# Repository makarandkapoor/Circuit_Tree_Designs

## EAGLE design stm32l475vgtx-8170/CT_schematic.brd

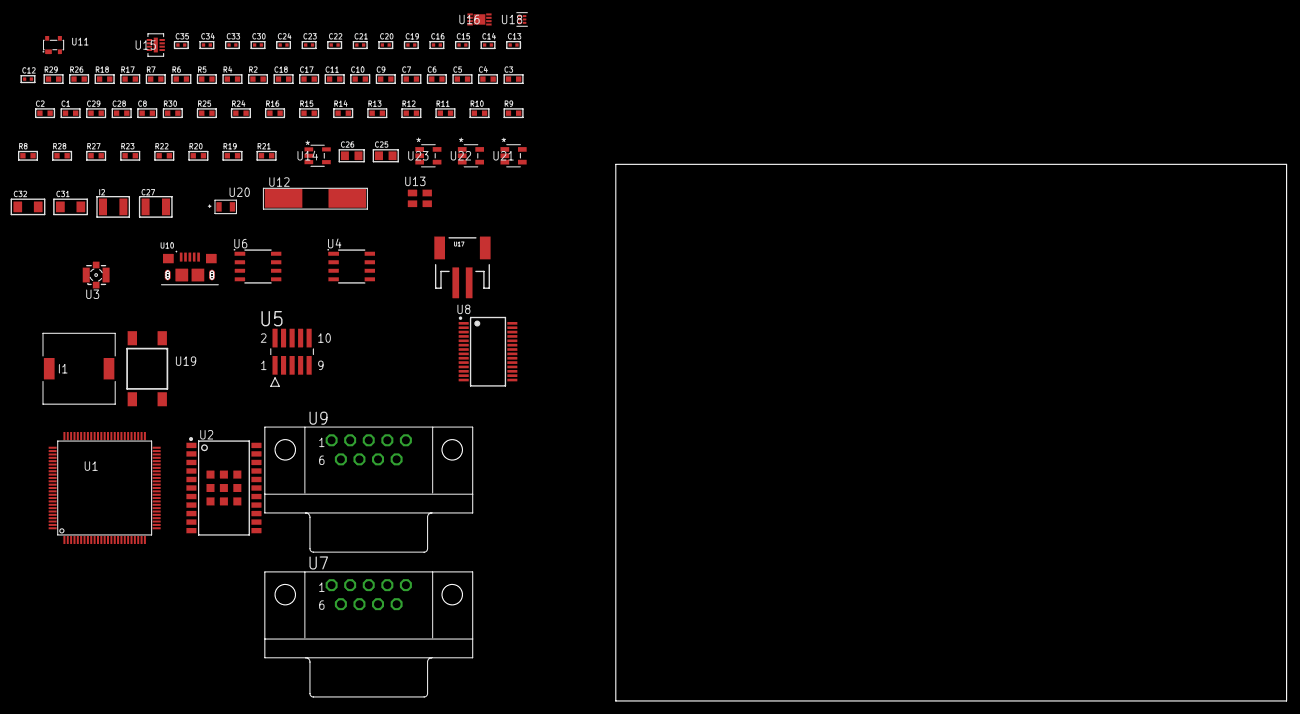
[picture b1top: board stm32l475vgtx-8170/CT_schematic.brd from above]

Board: 2 copper layers, 88 parts (0 on the bottom side), 65 nets, no tracks yet.

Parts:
C1, C11, C17, C18: 1e-06; C0603
C2, C3, C4, C5, C6, C7, C9: 1e-07; C0603
C8: 4.7e-06; C0603
C10: 1e-08; C0603
C12, C13: 1e-11; C0402
C14, C16, C19, C20, C21, C22, C23, C30: 1e-07; C0402
C15, C24, C33, C34, C35: 1e-08; C0402
C25, C26: 1e-05; C0805
C27: 1e-05; C1210
C28: 2.2e-06; C0603
C29: 2.2e-07; C0603
C31, C32: 1e-05; C1206
I1: 2.5e-06; DR1040
I2: 1e-05; L1210
R2: 1000.0; R0603
R4, R5: 4700.0; R0603
R6, R7: 2200.0; R0603
R8, R9, R10, R11, R12, R13, R14, R15, R16, R24, R25, R30: 10000.0; R0603
R17: 5.0; R0603
R18: 120.0; R0603
R19, R22: 100000.0; R0603
R20: 220000.0; R0603
R21: 1000000.0; R0603
R23: 560000.0; R0603
R26: 9100.0; R0603
R27: 680000.0; R0603
R28: 120000.0; R0603
R29: 2000.0; R0603
U1: STM32L475VGT6; LQFP100
U2: A2200-A
U3: 73412-0114; COAXIAL_C
U4: AT25M02-SSHD-T; SOIC-8
U5: FTSH-105-01-L-DV-K; SAMTEC_FTSH-105-01-L-DV-K
U6: MCP2562-E/SN; SOIC-8
U7, U9: 182-009-113R531; 182-009-MALE
U8: ST3241EBPR; SSOP-28
U10: 10118193-0001LF; FCI_10118193-0001LF
U11: prtr5v0u2ax; SOT143B
U12: ABLS-25.000MHZ-B2F-T
U13: ASEK-32.768KHz-ECST; ASEK
U14: ltc3406es5; TSOT-23-5
U15: LT3494AEDDB#TRMPBF; DFN-8_DDB
U16: MCP73831T-2ACI/MC; DFN8_2X3MC
U17: S2B-PH-SM4-TB(LF)(SN); JST-2-SMD
U18: TPS3895ADRYR; SON-6
U19: 4-1437565-2; SW_4-1437565-2
U20: Q65110A2395; LGM67K-G1J2-24-Z
U21, U22, U23: nc7sz125m5x; NC7SZ125M5X

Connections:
CLK_CRYSTAL_U1_12: C12.1, U1.12, U12.1
CLK_CRYSTAL_U1_13: C13.1, U1.13, U12.2
CLK_U1_8: U1.8, U13.3
GND: C1.2, C2.2, C3.2, C4.2, C5.2, C6.2, C7.2, C8.2, C9.2, C10.2, C11.2, C12.2, C13.2, C14.2, C15.2, C16.2, C17.2, C18.2, C19.2, C22.2, C23.2, C24.2, C25.2, C26.1, C26.2, C27.2, C28.2, C29.2, C30.2, C31.2, C32.2, C33.2, C34.2, C35.2, R2.2, R8.2, R16.2, R17.2, R20.2, R26.2, R28.2, R29.2, U1.10, U1.19, U1.20, U1.27, U1.49, U1.74, U1.99, U2.7, U2.8, U2.23, U2.24, U2.25, U2.26, U2.27, U2.28, U2.29, U2.30, U2.31, U4.4, U5.3, U5.5, U6.2, U6.8, U7.5, U8.23, U8.25, U9.5, U10.5, U10.6, U10.7, U10.8, U10.9, U11.1, U13.2, U14.2, U15.2, U15.9, U16.6, U16.9, U17.2, U18.2, U20.C, U21.2, U21.3, U22.1, U22.3, U23.1, U23.3
INPUT_USBPOWER_5V: C31.1, R30.2, U1.68, U10.1, U11.4, U16.1, U16.2
NET_U1_14: R5.1, U1.14, U23.4
NET_U1_92: R6.1, U1.92, U2.15
NET_U1_93: R7.1, U1.93, U2.16
NET_U1_94: R8.1, U1.94
NET_U1_98: U19.3, U19.4
NET_U2_2: R9.2, U2.2
NET_U2_17: R9.1, U2.17
NET_U2_22: R4.1, U2.22, U22.4
NET_U3_1: U2.11, U3.1
NET_U3_2: U2.10, U3.2, U3.3, U3.4
NET_U4_3: R10.1, U4.3
NET_U4_7: R12.1, U4.7
NET_U5_9: R17.1, U5.9
NET_U6_6: R18.2, U6.6
NET_U7_2: R18.2, U6.6, U7.2
NET_U7_3: R18.1, U6.7, U7.3
NET_U8_1: C21.1, U8.1
NET_U8_2: C21.2, U8.2
NET_U8_3: C23.1, U8.3
NET_U8_22: R19.1, U8.22
NET_U8_24: C20.2, U8.24
NET_U8_27: C22.1, U8.27
NET_U8_28: C20.1, U8.28
NET_U9_2: U8.4, U9.2
NET_U9_3: U8.9, U9.3
NET_U9_7: U8.5, U9.7
NET_U9_8: U8.10, U9.8
NET_U14_3: I1.1, U14.3
NET_U14_5: R20.1, R21.1, U14.5
NET_U14_ATNET_3: I1.2, R21.2
NET_U15_1: I2.1, U15.1
NET_U15_5: R22.1, U15.5
NET_U15_6: R23.1, U15.6
NET_U15_8: C29.1, U15.8
NET_U16_5: R30.1, U16.5
NET_U16_8: R29.1, U16.8
NET_U18_1: R25.1, R26.1, U18.1
NET_U18_3: R27.2, R28.1, U18.3
NET_U18_4: R24.1, U18.4, U21.4, U22.2, U23.2
NET_U19_1: R2.1, U19.1, U19.2
PROC_CAN1_RX: U1.81, U6.4
PROC_CAN1_TX: U1.82, U6.1
PROC_LPUART1_CTS: U1.52, U8.13
PROC_LPUART1_RTS: U1.51, U8.18
PROC_LPUART1_RX: U1.15, U8.19
PROC_LPUART1_TX: U1.16, U8.14
PROC_SPI1_MISO: U1.31, U4.2
PROC_SPI1_MOSI: U1.32, U4.5
PROC_SPI1_NSS: R11.1, U1.29, U4.1
PROC_SPI1_SCK: U1.30, U4.6
PROC_SYS_JTCK_SWCLK: R16.1, U1.76, U5.4
PROC_SYS_JTDI: R14.1, U1.77, U5.8
PROC_SYS_JTDO_SWO: U1.89, U5.6
PROC_SYS_JTMS_SWDIO: R15.1, U1.72, U5.2
PROC_USB_OTG_FS_DM: U1.70, U10.2, U11.3
PROC_USB_OTG_FS_DP: U1.71, U10.3, U11.2
RST_OUT_U5_JTAG_RST_B: R13.1, U5.10, U21.1
VCC_S1_3V7: C25.1, C27.1, C32.1, I2.2, R22.2, U14.4, U15.3, U15.4, U16.3, U16.4, U17.1
VCC_TIER1_3V3: C1.1, C2.1, C3.1, C4.1, C5.1, C6.1, C7.1, C8.1, C9.1, C10.1, C11.1, C14.1, C15.1, C16.1, C18.1, C19.1, C24.1, C26.2, C30.1, C33.1, C34.1, C35.1, I1.2, R4.2, R5.2, R6.2, R7.2, R10.2, R11.2, R12.2, R13.2, R14.2, R15.2, R19.2, R21.2, R24.2, R25.2, R27.1, U1.6, U1.11, U1.21, U1.22, U1.28, U1.50, U1.73, U1.75, U1.100, U2.20, U4.8, U5.1, U6.5, U8.26, U13.4, U18.6, U21.5, U22.5, U23.5
VCC_TIER1_5V0: C17.1, C28.1, R23.2, U6.3, U15.7

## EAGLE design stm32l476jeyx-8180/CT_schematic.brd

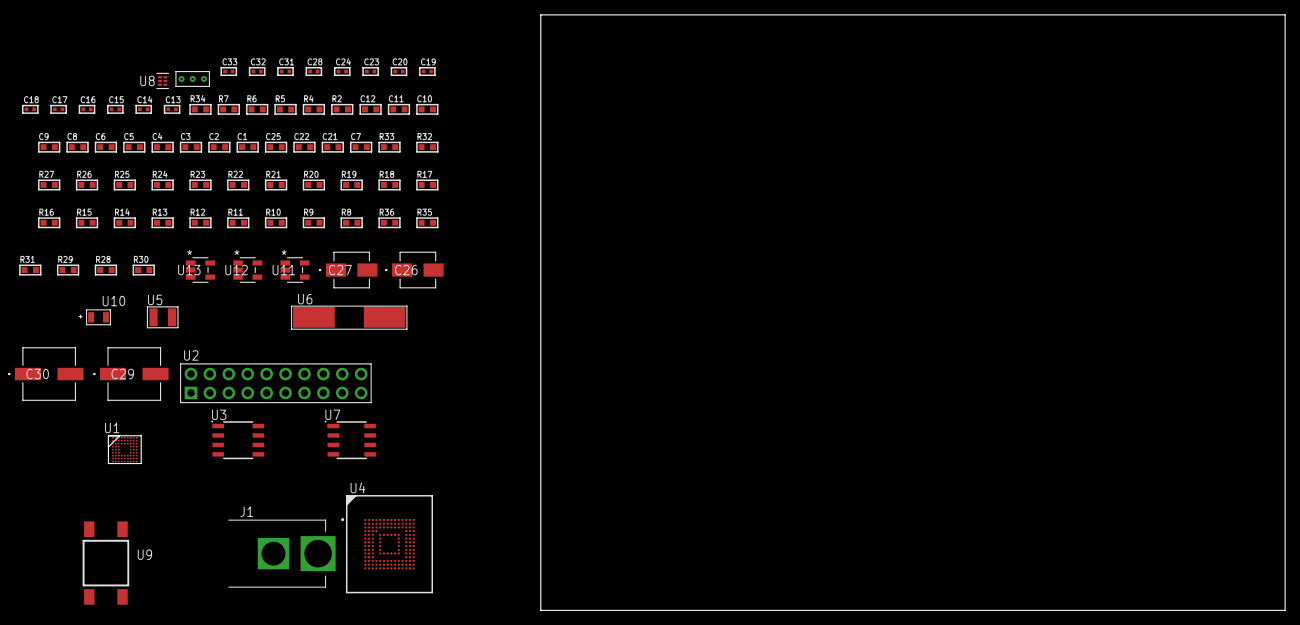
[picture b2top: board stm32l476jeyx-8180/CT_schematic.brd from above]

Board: 2 copper layers, 158.1 x 80.0 mm, 82 parts (0 on the bottom side), 43 nets, no tracks yet.

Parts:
C1, C12: 1e-06; C0603
C2, C3, C4, C5, C6, C8, C9, C10: 1e-07; C0603
C7: 4.7e-06; C0603
C11: 1e-08; C0603
C13, C14, C15, C16: 1e-11; C0402
C17, C18, C20, C23, C24, C28: 1e-07; C0402
C19, C31, C32, C33: 1e-08; C0402
C21, C22, C25: 2.2e-06; C0603
C26: 1e-06; EXV-9B
C27: 2.2e-06; EXV-9B
C29, C30: 0.0001; EXV-9H
J1: PJ-037B; PJ-037B_PACKAGE
R2: 1000.0; R0603
R4, R5: 4700.0; R0603
R6, R7: 2200.0; R0603
R8, R9, R10, R11, R12, R13, R14, R15, R16, R17, R32, R33: 10000.0; R0603
R18, R19, R20, R21, R22, R23, R24, R25, R26, R27: 34000.0; R0603
R28, R29, R31: 100000.0; R0603
R30: 164658.62; R0603
R34: 9100.0; R0603
R35: 680000.0; R0603
R36: 120000.0; R0603
U1: STM32L476JEY6; WLCSP72
U2: TST-110-05-T-D-RA
U3: 24AA1025T-I/SN; SOIC-8
U4: mtfc4gmcdm; TFBGA-153
U5: ABS07-32.768KHZ-7-T
U6: ABLS-25.000MHZ-B2F-T
U7: LP2954AIMX/NOPB; LP2954
U8: TPS3895ADRYR; SON-6
U9: 4-1437565-2; SW_4-1437565-2
U10: Q65110A2395; LGM67K-G1J2-24-Z
U11, U12, U13: nc7sz125m5x; NC7SZ125M5X
U14: Dummy; DUMMY_PACKAGE_186

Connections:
CLK_CRYSTAL_U1_C8: C13.1, U1.C8, U5.1
CLK_CRYSTAL_U1_C9: C14.1, U1.C9, U5.2
CLK_CRYSTAL_U1_D8: C15.1, U1.D8, U6.1
CLK_CRYSTAL_U1_D9: C16.1, U1.D9, U6.2
GND: C1.2, C2.2, C3.2, C4.2, C5.2, C6.2, C7.2, C8.2, C9.2, C10.2, C11.2, C12.2, C13.2, C14.2, C15.2, C16.2, C17.2, C18.2, C19.2, C20.2, C21.2, C22.2, C23.2, C24.2, C25.2, C26.2, C27.2, C28.2, C29.2, C30.2, C31.2, C32.2, C33.2, J1.2, R2.2, R8.2, R14.2, R17.2, R31.2, R34.2, R36.2, U1.A8, U1.B1, U1.G9, U1.J2, U1.J9, U2.4, U2.6, U2.8, U2.10, U2.12, U2.14, U2.16, U2.18, U2.20, U3.4, U3.7, U4.C4, U4.E7, U4.G5, U4.H10, U4.K8, U4.N2, U4.N5, U4.P4, U4.P6, U7.4, U8.2, U10.C, U11.2, U11.3, U12.1, U12.3, U13.1, U13.3, U14.1
NET_U1_A5: R6.1, U1.A5, U3.6
NET_U1_A7: R7.1, U1.A7, U3.5
NET_U1_D7: R8.1, U1.D7
NET_U1_E9: R5.1, U1.E9, U13.4
NET_U1_J7: U9.3, U9.4
NET_U2_19: R14.1, U2.19
NET_U3_1: R16.1, U3.1
NET_U3_2: R17.1, U3.2
NET_U3_3: R15.1, U3.3
NET_U4_C2: C22.1, C23.1, U4.C2
NET_U4_K5: R4.1, U4.K5, U12.4
NET_U7_3: R29.1, U7.3
NET_U7_5: R28.1, U7.5
NET_U7_7: R30.2, R31.1, U7.7
NET_U8_1: R33.1, R34.1, U8.1
NET_U8_3: R35.2, R36.1, U8.3
NET_U8_4: R32.1, U8.4, U11.4, U12.2, U13.2
NET_U9_1: R2.1, U9.1, U9.2
PROC_PG9: U1.A4, U14.2
PROC_PG10: U1.B4, U14.3
PROC_SDMMC1_CK: R27.1, U1.B3, U4.M6
PROC_SDMMC1_CMD: R26.1, U1.A3, U4.M5
PROC_SDMMC1_D0: R18.1, U1.F2, U4.A3
PROC_SDMMC1_D1: R19.1, U1.E1, U4.A4
PROC_SDMMC1_D2: R20.1, U1.D3, U4.A5
PROC_SDMMC1_D3: R21.1, U1.C3, U4.B2
PROC_SDMMC1_D4: R22.1, U1.E7, U4.B3
PROC_SDMMC1_D5: R23.1, U1.E8, U4.B4
PROC_SDMMC1_D6: R24.1, U1.F3, U4.B5
PROC_SDMMC1_D7: R25.1, U1.F1, U4.B6
PROC_SYS_JTCK_SWCLK: R12.1, U1.B2, U2.9
PROC_SYS_JTDI: R10.1, U1.A2, U2.5
PROC_SYS_JTDO_SWO: U1.A6, U2.13
PROC_SYS_JTMS_SWDIO: R11.1, U1.C2, U2.7
PROC_SYS_JTRST: R9.1, U1.C6, U2.3
RST_OUT_U2_SRESET_B: R13.1, U2.15, U11.1
VCC_S1_5V2: C26.1, C29.1, C30.1, J1.1, R29.2, U7.8
VCC_TIER1_3V3: C1.1, C2.1, C3.1, C4.1, C5.1, C6.1, C7.1, C8.1, C9.1, C10.1, C11.1, C12.1, C17.1, C18.1, C19.1, C20.1, C21.1, C24.1, C25.1, C27.1, C28.1, C31.1, C32.1, C33.1, R4.2, R5.2, R6.2, R7.2, R9.2, R10.2, R11.2, R12.2, R13.2, R15.2, R16.2, R18.2, R19.2, R20.2, R21.2, R22.2, R23.2, R24.2, R25.2, R26.2, R27.2, R28.2, R30.1, R32.2, R33.2, R35.1, U1.A1, U1.A9, U1.B6, U1.B9, U1.G8, U1.H9, U1.J1, U1.J8, U2.1, U2.2, U3.8, U4.C6, U4.E6, U4.F5, U4.J10, U4.K9, U4.M4, U4.N4, U4.P3, U4.P5, U7.1, U8.6, U11.5, U12.5, U13.5

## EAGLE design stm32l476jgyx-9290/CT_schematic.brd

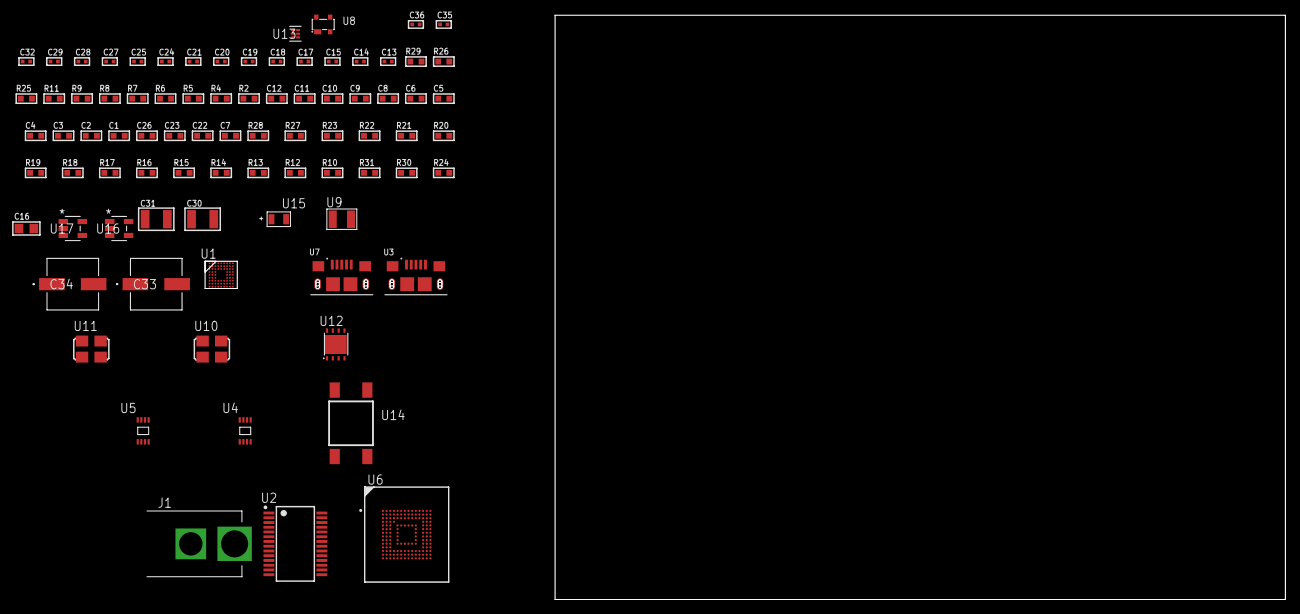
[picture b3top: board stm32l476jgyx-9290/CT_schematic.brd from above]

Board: 2 copper layers, 83 parts (0 on the bottom side), 46 nets, no tracks yet.

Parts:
C1, C12: 1e-06; C0603
C2, C3, C4, C5, C6, C8, C9, C10: 1e-07; C0603
C7: 4.7e-06; C0603
C11: 1e-08; C0603
C13, C14: 1e-11; C0402
C15, C17, C18, C21, C24, C25, C32: 1e-07; C0402
C16: 4.7e-06; C0805
C19, C20, C27, C28, C29, C35, C36: 1e-08; C0402
C22, C23, C26: 2.2e-06; C0603
C30, C31: 1e-05; C1210
C33, C34: 0.0001; EXV-9H
J1: PJ-037B; PJ-037B_PACKAGE
R2, R26: 1000.0; R0603
R4, R5, R11: 4700.0; R0603
R6, R7, R8, R9: 2200.0; R0603
R10, R12, R13, R27, R28: 10000.0; R0603
R14, R15, R16, R17, R18, R19, R20, R21, R22, R23: 34000.0; R0603
R24: 100000.0; R0603
R25: 2231.0; R0603
R29: 9100.0; R0603
R30: 680000.0; R0603
R31: 120000.0; R0603
U1: STM32L476JGY7; WLCSP72
U2: FT232RL-REEL; SSOP-28
U3, U7: 10118193-0001LF; FCI_10118193-0001LF
U4: 24AA01T-I/MNY; TDFN-8/6MM
U5: 24AA02T-I/MNY; TDFN-8/6MM
U6: mtfc4gmcdm; TFBGA-153
U8: prtr5v0u2ax; SOT143B
U9: ABS07-32.768KHZ-7-T
U10: ASFL1-12MHZ-NCS; ASFL1
U11: ASFL1-25MHZ-NCS; ASFL1
U12: LP3878SDX-ADJ/NOPB; WSON-8
U13: TPS3895ADRYR; SON-6
U14: 4-1437565-2; SW_4-1437565-2
U15: Q65110A2395; LGM67K-G1J2-24-Z
U16, U17: nc7sz125m5x; NC7SZ125M5X

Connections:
CLK_CRYSTAL_U1_C8: C13.1, U1.C8, U9.1
CLK_CRYSTAL_U1_C9: C14.1, U1.C9, U9.2
CLK_U1_D9: U1.D9, U11.3
CLK_U2_27: U2.27, U10.3
GND: C1.2, C2.2, C3.2, C4.2, C5.2, C6.2, C7.2, C8.2, C9.2, C10.2, C11.2, C12.2, C13.2, C14.2, C15.2, C16.2, C17.2, C18.2, C19.2, C20.2, C21.2, C22.2, C23.2, C24.2, C25.2, C26.2, C27.2, C28.2, C29.2, C30.2, C31.2, C32.2, C33.2, C34.2, C35.2, C36.2, J1.2, R2.2, R10.2, R13.2, R26.2, R29.2, R31.2, U1.A8, U1.B1, U1.G9, U1.J2, U1.J9, U2.7, U2.18, U2.21, U2.25, U2.26, U3.5, U3.6, U3.7, U3.8, U3.9, U4.4, U4.7, U5.4, U5.7, U6.C4, U6.E7, U6.G5, U6.H10, U6.K8, U6.N2, U6.N5, U6.P4, U6.P6, U7.5, U7.6, U7.7, U7.8, U7.9, U8.1, U10.2, U11.2, U12.3, U12.PAD, U13.2, U15.C, U16.1, U16.3, U17.1, U17.3
NET_U1_A5: R6.1, U1.A5, U4.6
NET_U1_A7: R7.1, U1.A7, U4.5
NET_U1_D7: R10.1, U1.D7
NET_U1_E9: R5.1, U1.E9, U17.4
NET_U1_G2: R9.1, U1.G2, U5.5
NET_U1_H3: R8.1, U1.H3, U5.6
NET_U1_J7: U14.3, U14.4
NET_U2_14: R12.1, U2.14
NET_U2_17: C17.1, U2.17
NET_U2_19: R13.1, U2.19
NET_U3_1: R11.1, U3.1
NET_U3_2: U2.16, U3.2
NET_U3_3: U2.15, U3.3
NET_U6_C2: C23.1, C24.1, U6.C2
NET_U6_K5: R4.1, U6.K5, U16.4
NET_U12_1: C29.1, U12.1
NET_U12_6: R25.2, R26.1, U12.6
NET_U12_8: R24.1, U12.8
NET_U13_1: R28.1, R29.1, U13.1
NET_U13_3: R30.2, R31.1, U13.3
NET_U13_4: R27.1, U13.4, U16.2, U17.2
NET_U14_1: R2.1, U14.1, U14.2
PROC_LPUART1_CTS: U1.H2, U2.3
PROC_LPUART1_RTS: U1.H1, U2.11
PROC_LPUART1_RX: U1.F9, U2.1
PROC_LPUART1_TX: U1.F8, U2.5
PROC_SDMMC1_CK: R23.1, U1.B3, U6.M6
PROC_SDMMC1_CMD: R22.1, U1.A3, U6.M5
PROC_SDMMC1_D0: R14.1, U1.F2, U6.A3
PROC_SDMMC1_D1: R15.1, U1.E1, U6.A4
PROC_SDMMC1_D2: R16.1, U1.D3, U6.A5
PROC_SDMMC1_D3: R17.1, U1.C3, U6.B2
PROC_SDMMC1_D4: R18.1, U1.E7, U6.B3
PROC_SDMMC1_D5: R19.1, U1.E8, U6.B4
PROC_SDMMC1_D6: R20.1, U1.F3, U6.B5
PROC_SDMMC1_D7: R21.1, U1.F1, U6.B6
PROC_USB_OTG_FS_DM: U1.D1, U7.2, U8.3
PROC_USB_OTG_FS_DP: U1.C1, U7.3, U8.2
PROC_USB_OTG_FS_VBUS: U1.E3, U7.1, U8.4
VCC_S1_14V6: C30.1, C33.1, C34.1, J1.1, R24.2, U12.4
VCC_TIER1_3V3: C1.1, C2.1, C3.1, C4.1, C5.1, C6.1, C7.1, C8.1, C9.1, C10.1, C11.1, C12.1, C15.1, C16.1, C18.1, C19.1, C20.1, C21.1, C22.1, C25.1, C26.1, C27.1, C28.1, C31.1, C32.1, C35.1, C36.1, R4.2, R5.2, R6.2, R7.2, R8.2, R9.2, R12.2, R14.2, R15.2, R16.2, R17.2, R18.2, R19.2, R20.2, R21.2, R22.2, R23.2, R25.1, R27.2, R28.2, R30.1, U1.A1, U1.A9, U1.B6, U1.B9, U1.G8, U1.H9, U1.J1, U1.J8, U2.4, U2.20, U4.8, U5.8, U6.C6, U6.E6, U6.F5, U6.J10, U6.K9, U6.M4, U6.N4, U6.P3, U6.P5, U10.4, U11.4, U12.5, U13.6, U16.5, U17.5

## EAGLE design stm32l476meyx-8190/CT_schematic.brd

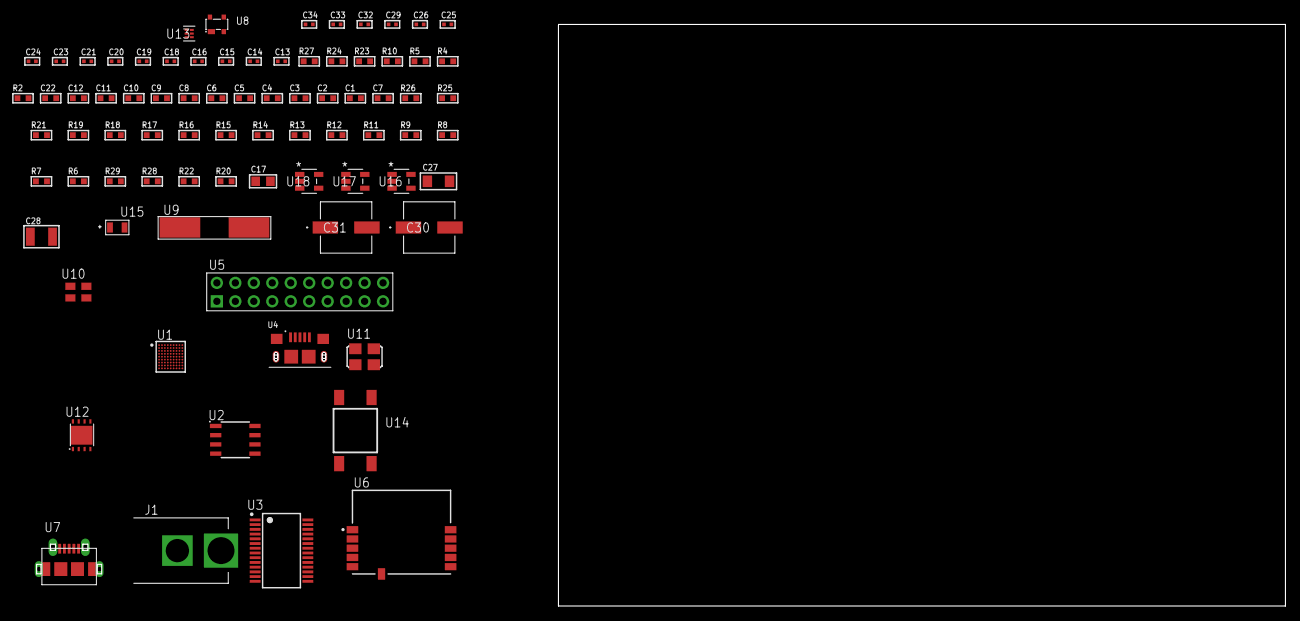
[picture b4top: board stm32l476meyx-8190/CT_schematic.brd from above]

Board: 2 copper layers, 171.8 x 80.0 mm, 80 parts (0 on the bottom side), 50 nets, no tracks yet.

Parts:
C1, C12, C22: 1e-06; C0603
C2, C3, C4, C5, C6, C8, C9, C10: 1e-07; C0603
C7: 4.7e-06; C0603
C11: 1e-08; C0603
C13, C14: 1e-11; C0402
C15, C24, C25, C26, C32, C33, C34: 1e-08; C0402
C16, C18, C19, C20, C21, C23, C29: 1e-07; C0402
C17: 4.7e-06; C0805
C27: 1e-05; C1206
C28: 1e-05; C1210
C30, C31: 0.0001; EXV-9H
J1: PJ-037B; PJ-037B_PACKAGE
R2, R24: 1000.0; R0603
R4, R5, R10: 4700.0; R0603
R6, R7, R8, R9, R11, R12, R13, R14, R15, R16, R17, R18, R19, R25, R26: 10000.0; R0603
R20, R22: 100000.0; R0603
R21: 47000.0; R0603
R23: 2231.0; R0603
R27: 9100.0; R0603
R28: 680000.0; R0603
R29: 120000.0; R0603
U1: STM32L476MEY6; WLCSP81
U2: AT25128B-SSHL-T; SOIC-8
U3: FT232RL-REEL; SSOP-28
U4: 10118193-0001LF; FCI_10118193-0001LF
U5: TST-110-05-T-D-RA
U6: SPBTLE-RF; XCVR_SPBTLE-RF
U7: 47590-0001; MICRO_USB_AB
U8: prtr5v0u2ax; SOT143B
U9: ABLS-25.000MHZ-B2F-T
U10: ASEK-32.768KHz-ECST; ASEK
U11: ASFL1-12MHZ-NCS; ASFL1
U12: LP3878SDX-ADJ/NOPB; WSON-8
U13: TPS3895ADRYR; SON-6
U14: 4-1437565-2; SW_4-1437565-2
U15: Q65110A2395; LGM67K-G1J2-24-Z
U16, U17, U18: nc7sz125m5x; NC7SZ125M5X

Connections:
CLK_CRYSTAL_U1_D8: C13.1, U1.D8, U9.1
CLK_CRYSTAL_U1_D9: C14.1, U1.D9, U9.2
CLK_U1_C9: U1.C9, U10.3
CLK_U3_27: U3.27, U11.3
GND: C1.2, C2.2, C3.2, C4.2, C5.2, C6.2, C7.2, C8.2, C9.2, C10.2, C11.2, C12.2, C13.2, C14.2, C15.2, C16.2, C17.2, C18.2, C19.2, C20.2, C21.2, C22.2, C23.2, C24.2, C25.2, C26.2, C27.2, C28.2, C29.2, C30.2, C31.2, C32.2, C33.2, C34.2, J1.2, R2.2, R6.2, R12.2, R18.2, R20.2, R21.2, R24.2, R27.2, R29.2, U1.A8, U1.B1, U1.G9, U1.J2, U1.J9, U2.4, U3.7, U3.18, U3.21, U3.25, U3.26, U4.5, U4.6, U4.7, U4.8, U4.9, U5.4, U5.6, U5.8, U5.10, U5.12, U5.14, U5.16, U5.18, U5.20, U6.6, U7.5, U7.6, U7.7, U7.8, U7.9, U8.1, U10.2, U11.2, U12.3, U12.PAD, U13.2, U15.C, U16.2, U16.3, U17.1, U17.3, U18.1, U18.3
NET_U1_D7: R6.1, U1.D7
NET_U1_E9: R5.1, U1.E9, U18.4
NET_U1_J7: U14.3, U14.4
NET_U2_3: R7.1, U2.3
NET_U2_7: R9.1, U2.7
NET_U3_14: R11.1, U3.14
NET_U3_17: C18.1, U3.17
NET_U3_19: R12.1, U3.19
NET_U4_1: R10.1, U4.1
NET_U4_2: U3.16, U4.2
NET_U4_3: U3.15, U4.3
NET_U5_19: R18.1, U5.19
NET_U6_11: R4.1, U6.11, U17.4
NET_U12_1: C26.1, U12.1
NET_U12_6: R23.2, R24.1, U12.6
NET_U12_8: R22.1, U12.8
NET_U13_1: R26.1, R27.1, U13.1
NET_U13_3: R28.2, R29.1, U13.3
NET_U13_4: R25.1, U13.4, U16.4, U17.2, U18.2
NET_U14_1: R2.1, U14.1, U14.2
PROC_GPIO_TO_U6_SPI_IRQ: R21.1, U1.A3, U6.4
PROC_LPUART1_CTS: U1.H2, U3.3
PROC_LPUART1_RTS: U1.H1, U3.11
PROC_LPUART1_RX: U1.F9, U3.1
PROC_LPUART1_TX: U1.F8, U3.5
PROC_SPI1_MISO: U1.H5, U6.8
PROC_SPI1_MOSI: U1.C7, U6.9
PROC_SPI1_NSS: R19.1, U1.G5, U6.10
PROC_SPI1_SCK: R20.1, U1.H6, U6.7
PROC_SPI2_MISO: U1.F7, U2.2
PROC_SPI2_MOSI: U1.E5, U2.5
PROC_SPI2_NSS: R8.1, U1.E8, U2.1
PROC_SPI2_SCK: U1.H3, U2.6
PROC_SYS_JTCK_SWCLK: R16.1, U1.B2, U5.9
PROC_SYS_JTDI: R14.1, U1.A2, U5.5
PROC_SYS_JTDO_SWO: U1.A6, U5.13
PROC_SYS_JTMS_SWDIO: R15.1, U1.C2, U5.7
PROC_SYS_JTRST: R13.1, U1.C6, U5.3
PROC_USB_OTG_FS_DM: U1.D1, U7.2, U8.3
PROC_USB_OTG_FS_DP: U1.C1, U7.3, U8.2
PROC_USB_OTG_FS_ID: U1.D2, U7.4
PROC_USB_OTG_FS_VBUS: U1.E3, U7.1, U8.4
RST_OUT_U5_SRESET_B: R17.1, U5.15, U16.1
VCC_S1_10V0: C27.1, C30.1, C31.1, J1.1, R22.2, U12.4
VCC_TIER1_3V3: C1.1, C2.1, C3.1, C4.1, C5.1, C6.1, C7.1, C8.1, C9.1, C10.1, C11.1, C12.1, C15.1, C16.1, C17.1, C19.1, C20.1, C21.1, C22.1, C23.1, C24.1, C25.1, C28.1, C29.1, C32.1, C33.1, C34.1, R4.2, R5.2, R7.2, R8.2, R9.2, R11.2, R13.2, R14.2, R15.2, R16.2, R17.2, R19.2, R23.1, R25.2, R26.2, R28.1, U1.A1, U1.A9, U1.B6, U1.B9, U1.E4, U1.G8, U1.H9, U1.J1, U1.J8, U2.8, U3.4, U3.20, U5.1, U5.2, U6.5, U10.4, U11.4, U12.5, U13.6, U16.5, U17.5, U18.5

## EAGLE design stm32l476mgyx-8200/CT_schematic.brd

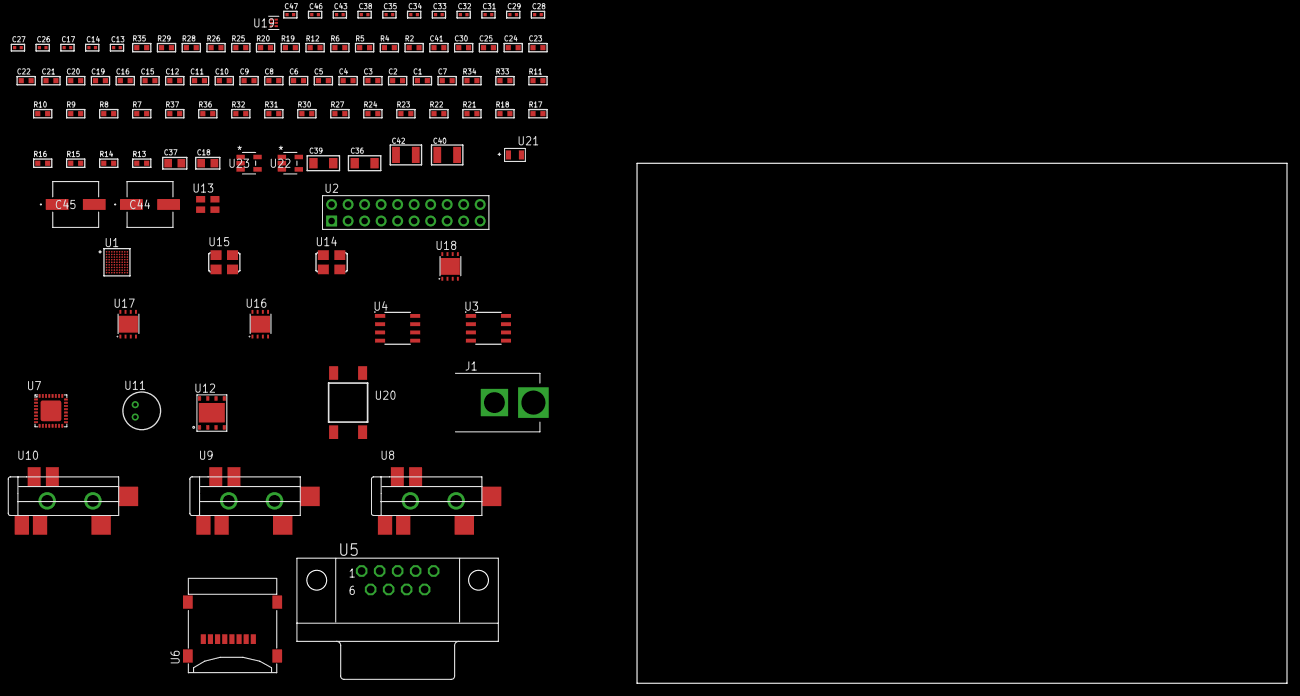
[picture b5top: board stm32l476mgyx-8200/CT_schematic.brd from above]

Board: 2 copper layers, 100.0 x 80.0 mm, 106 parts (0 on the bottom side), 65 nets, no tracks yet.

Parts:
C1, C12, C15, C16, C19, C20, C21, C22, C23, C24, C25, C30, C41: 1e-06; C0603
C2, C3, C4, C5, C6, C8, C9, C10: 1e-07; C0603
C7: 4.7e-06; C0603
C11: 1e-08; C0603
C13, C17, C26, C27, C28, C29, C31, C43: 1e-07; C0402
C14, C32, C33, C34, C35, C38, C46, C47: 1e-08; C0402
C18, C37: 1e-05; C0805
C36, C39: 1e-05; C1206
C40, C42: 1e-05; C1210
C44, C45: 0.0001; EXV-9H
J1: PJ-037B; PJ-037B_PACKAGE
R2, R26, R29: 1000.0; R0603
R4: 4700.0; R0603
R5, R6: 2200.0; R0603
R7, R8, R9, R10, R11, R33, R34: 10000.0; R0603
R12: 120.0; R0603
R13, R14, R15, R16, R17, R18, R21, R22, R23, R24, R27, R30, R32: 100000.0; R0603
R19, R20: 1270.0; R0603
R25: 200.0; R0603
R28: 2231.0; R0603
R31: 300000.0; R0603
R35: 9100.0; R0603
R36: 680000.0; R0603
R37: 120000.0; R0603
U1: STM32L476MGY6; WLCSP81
U2: TST-110-05-T-D-RA
U3: 24AA1025T-I/SN; SOIC-8
U4: MCP2562-E/SN; SOIC-8
U5: 182-009-113R531; 182-009-MALE
U6: 0472192001; MOLEX_47219-2001
U7: SGTL5000XNAA3; QFN-32
U8, U9, U10: SJ-43515TS-SMT-TR
U11: WM-64PCT; WM-64PC
U12: SST26VF032B-104I/MF; WFDN-8
U13: ASEK-32.768KHz-ECST; ASEK
U14: ASFL-24.57MHZ-NCS; ASFL1
U15: ASFL1-25MHZ-NCS; ASFL1
U16, U17: LP3878SDX-ADJ/NOPB; WSON-8
U18: LP2951ACSDX/NOPB; WSON-8
U19: TPS3895ADRYR; SON-6
U20: 4-1437565-2; SW_4-1437565-2
U21: Q65110A2395; LGM67K-G1J2-24-Z
U22, U23: nc7sz125m5x; NC7SZ125M5X

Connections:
CLK_U1_C9: U1.C9, U13.3
CLK_U1_D9: U1.D9, U15.3
CLK_U7_21: U7.21, U14.3
GND: C1.2, C2.2, C3.2, C4.2, C5.2, C6.2, C7.2, C8.2, C9.2, C10.2, C11.2, C12.2, C13.2, C14.2, C15.2, C16.2, C17.2, C18.2, C26.2, C27.2, C28.2, C29.2, C30.2, C31.2, C32.2, C33.2, C34.2, C35.2, C36.2, C37.2, C38.2, C39.2, C40.2, C41.2, C42.2, C43.2, C44.2, C45.2, C46.2, C47.2, J1.2, R2.2, R7.2, R20.2, R26.2, R29.2, R32.2, R35.2, R37.2, U1.A8, U1.B1, U1.G9, U1.J2, U1.J9, U2.4, U2.6, U2.8, U2.10, U2.12, U2.14, U2.16, U2.18, U2.20, U3.4, U3.7, U4.2, U4.8, U5.5, U6.6, U6.G1, U6.G2, U6.G3, U6.G4, U7.1, U7.3, U7.7, U7.EXP, U9.1, U10.1, U11.2, U12.4, U12.9, U13.2, U14.2, U15.2, U16.3, U16.PAD, U17.3, U17.PAD, U18.3, U18.4, U18.PAD, U19.2, U21.C, U22.2, U22.3, U23.1, U23.3
NET_U1_A5: R5.1, U1.A5, U3.6
NET_U1_A7: R6.1, U1.A7, U3.5
NET_U1_D7: R7.1, U1.D7
NET_U1_E9: R4.1, U1.E9, U23.4
NET_U1_J7: U20.3, U20.4
NET_U3_1: R10.1, U3.1
NET_U3_2: R11.1, U3.2
NET_U3_3: R9.1, U3.3
NET_U4_6: R12.2, U4.6
NET_U5_2: R12.2, U4.6, U5.2
NET_U5_3: R12.1, U4.7, U5.3
NET_U7_10: C29.1, U7.10
NET_U7_29: R19.1, U7.29
NET_U7_31: R20.1, U7.31
NET_U8_1: U7.4, U8.1
NET_U8_2: U7.2, U8.2
NET_U8_5: U7.6, U8.5
NET_U9_2: C20.1, U9.2
NET_U9_5: C19.1, U9.5
NET_U10_2: C22.1, C23.1, U10.2
NET_U10_5: C21.1, U10.5
NET_U10_13: C22.2, C23.2
NET_U11_1: C24.1, C25.1, C30.1, U7.16, U11.1
NET_U11_15: C24.2, C25.2
NET_U16_1: C35.1, U16.1
NET_U16_6: R25.2, R26.1, U16.6
NET_U16_8: R24.1, U16.8
NET_U17_1: C38.1, U17.1
NET_U17_6: R28.2, R29.1, U17.6
NET_U17_8: R27.1, U17.8
NET_U18_5: R30.1, U18.5
NET_U18_7: R31.2, R32.1, U18.7
NET_U19_1: R34.1, R35.1, U19.1
NET_U19_3: R36.2, R37.1, U19.3
NET_U19_4: R33.1, U19.4, U22.4, U23.2
NET_U20_1: R2.1, U20.1, U20.2
PROC_CAN1_RX: U1.D1, U4.4
PROC_CAN1_TX: U1.C1, U4.1
PROC_QUADSPI_BK1_IO0: U1.J4, U12.5
PROC_QUADSPI_BK1_IO1: U1.J5, U12.2
PROC_QUADSPI_BK1_IO2: R22.1, U1.H4, U12.3
PROC_QUADSPI_BK1_IO3: R23.1, U1.H5, U12.7
PROC_QUADSPI_CLK: U1.H3, U12.6
PROC_QUADSPI_NCS: R21.1, U1.G3, U12.1
PROC_SAI1_FS_B: U1.B7, U7.23
PROC_SAI1_SCK_B: U1.F6, U7.24
PROC_SAI1_SD_B: U1.C7, U7.26
PROC_SDMMC1_CK: R14.1, U1.B3, U6.5
PROC_SDMMC1_CMD: R13.1, U1.A3, U6.3
PROC_SDMMC1_D0: R15.1, U1.F2, U6.7
PROC_SDMMC1_D1: R16.1, U1.E1, U6.8
PROC_SDMMC1_D2: R17.1, U1.D3, U6.1
PROC_SDMMC1_D3: R18.1, U1.C3, U6.2
PROC_SYS_JTCK_SWCLK: U1.B2, U2.9
PROC_SYS_JTDO_SWO: U1.A6, U2.13
PROC_SYS_JTMS_SWDIO: U1.C2, U2.7
RST_OUT_U2_SRESET_B: R8.1, U2.15, U22.1
VCC_S1_6V5: C36.1, C39.1, C41.1, C44.1, C45.1, J1.1, R24.2, R27.2, U16.4, U17.4, U18.8
VCC_TIER1_1V2: C26.1, C37.1, R25.1, U7.30, U16.5
VCC_TIER1_3V3: C1.1, C2.1, C3.1, C4.1, C5.1, C6.1, C7.1, C8.1, C9.1, C10.1, C11.1, C12.1, C13.1, C14.1, C16.1, C17.1, C18.1, C27.1, C28.1, C31.1, C32.1, C33.1, C34.1, C40.1, C43.1, C46.1, C47.1, R4.2, R5.2, R6.2, R8.2, R9.2, R10.2, R11.2, R13.2, R14.2, R15.2, R16.2, R17.2, R18.2, R19.2, R21.2, R22.2, R23.2, R28.1, R33.2, R34.2, R36.1, U1.A1, U1.A9, U1.B6, U1.B9, U1.E4, U1.G8, U1.H9, U1.J1, U1.J8, U2.1, U3.8, U4.5, U6.4, U7.5, U7.20, U12.8, U13.4, U14.4, U15.4, U17.5, U19.6, U22.5, U23.5
VCC_TIER1_5V0: C15.1, C42.1, R30.2, R31.1, U4.3, U18.1

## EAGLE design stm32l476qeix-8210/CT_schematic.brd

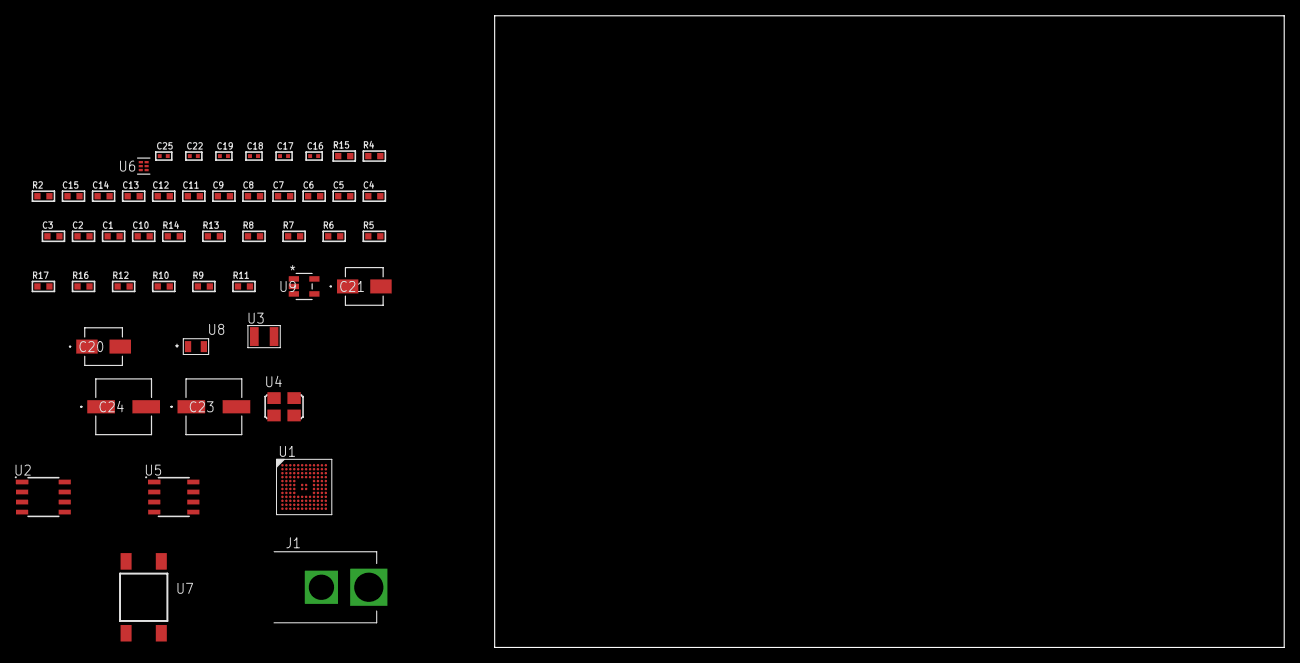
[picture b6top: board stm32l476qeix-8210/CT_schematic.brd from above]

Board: 2 copper layers, 100.0 x 80.0 mm, 50 parts (0 on the bottom side), 22 nets, no tracks yet.

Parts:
C1, C15: 1e-06; C0603
C2, C3, C4, C5, C6, C7, C8, C9, C11, C12, C13: 1e-07; C0603
C10: 4.7e-06; C0603
C14: 1e-08; C0603
C16, C17: 1e-11; C0402
C18, C19, C25: 1e-08; C0402
C20: 1e-06; EXV-9B
C21: 2.2e-06; EXV-9B
C22: 1e-07; C0402
C23, C24: 0.0001; EXV-9H
J1: PJ-037B; PJ-037B_PACKAGE
R2: 1000.0; R0603
R4: 4700.0; R0603
R5, R6, R7, R8, R13, R14: 10000.0; R0603
R9, R10, R12: 100000.0; R0603
R11: 164658.62; R0603
R15: 9100.0; R0603
R16: 680000.0; R0603
R17: 120000.0; R0603
U1: STM32L476QEI6; UFBGA132
U2: AT25010B-SSHL-T; SOIC-8
U3: ABS07-32.768KHZ-7-T
U4: ASFL1-25MHZ-NCS; ASFL1
U5: LP2954AIMX/NOPB; LP2954
U6: TPS3895ADRYR; SON-6
U7: 4-1437565-2; SW_4-1437565-2
U8: Q65110A2395; LGM67K-G1J2-24-Z
U9: nc7sz125m5x; NC7SZ125M5X

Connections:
CLK_CRYSTAL_U1_D1: C16.1, U1.D1, U3.1
CLK_CRYSTAL_U1_E1: C17.1, U1.E1, U3.2
CLK_U1_F1: U1.F1, U4.3
GND: C1.2, C2.2, C3.2, C4.2, C5.2, C6.2, C7.2, C8.2, C9.2, C10.2, C11.2, C12.2, C13.2, C14.2, C15.2, C16.2, C17.2, C18.2, C19.2, C20.2, C21.2, C22.2, C23.2, C24.2, C25.2, J1.2, R2.2, R5.2, R12.2, R15.2, R17.2, U1.D3, U1.E3, U1.F2, U1.F6, U1.F7, U1.F11, U1.F12, U1.J1, U2.4, U4.2, U5.4, U6.2, U8.C, U9.1, U9.3
NET_U1_A4: R5.1, U1.A4
NET_U1_H2: R4.1, U1.H2, U9.4
NET_U1_M12: U7.3, U7.4
NET_U2_3: R6.1, U2.3
NET_U2_7: R8.1, U2.7
NET_U5_3: R10.1, U5.3
NET_U5_5: R9.1, U5.5
NET_U5_7: R11.2, R12.1, U5.7
NET_U6_1: R14.1, R15.1, U6.1
NET_U6_3: R16.2, R17.1, U6.3
NET_U6_4: R13.1, U6.4, U9.2
NET_U7_1: R2.1, U7.1, U7.2
PROC_SPI1_MISO: U1.A7, U2.2
PROC_SPI1_MOSI: U1.C5, U2.5
PROC_SPI1_NSS: R7.1, U1.A9, U2.1
PROC_SPI1_SCK: U1.A8, U2.6
VCC_S1_9V9: C20.1, C23.1, C24.1, J1.1, R10.2, U5.8
VCC_TIER1_3V3: C1.1, C2.1, C3.1, C4.1, C5.1, C6.1, C7.1, C8.1, C9.1, C10.1, C11.1, C12.1, C13.1, C14.1, C15.1, C18.1, C19.1, C21.1, C22.1, C25.1, R4.2, R6.2, R7.2, R8.2, R9.2, R11.1, R13.2, R14.2, R16.1, U1.C4, U1.C11, U1.E2, U1.G2, U1.G6, U1.G7, U1.G11, U1.G12, U1.H3, U1.L1, U1.M1, U2.8, U4.4, U5.1, U6.6, U9.5

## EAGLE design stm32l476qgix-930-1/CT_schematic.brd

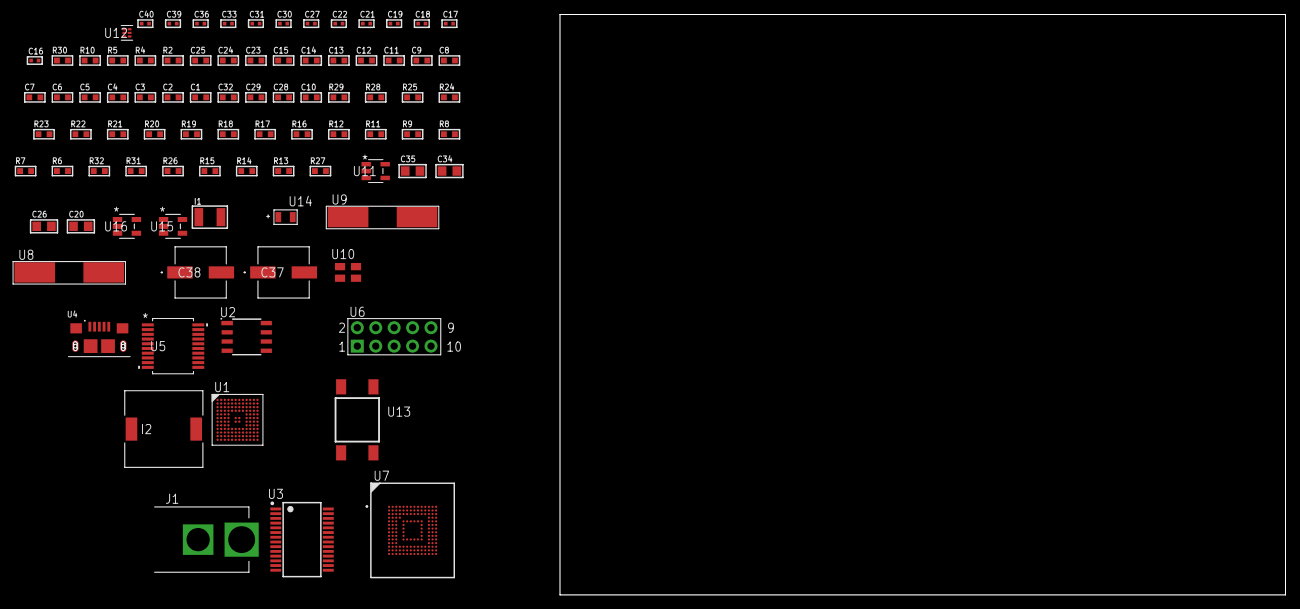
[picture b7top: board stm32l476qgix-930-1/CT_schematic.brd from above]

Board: 2 copper layers, 167.1 x 80.0 mm, 89 parts (0 on the bottom side), 62 nets, no tracks yet.

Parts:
C1, C15, C23, C24, C25: 1e-06; C0603
C2, C3, C4, C5, C6, C7, C8, C9, C11, C12, C13: 1e-07; C0603
C10: 4.7e-06; C0603
C14: 1e-08; C0603
C16, C17: 1e-11; C0402
C18, C33, C39, C40: 1e-08; C0402
C19, C21, C22, C27, C30, C31, C36: 1e-07; C0402
C20, C26: 4.7e-06; C0805
C28, C29, C32: 2.2e-06; C0603
C34, C35: 1e-05; C0805
C37, C38: 0.0001; EXV-9H
I1: 1.5e-05; L1210
I2: 5.2e-06; DR1040
J1: PJ-037B; PJ-037B_PACKAGE
R2: 1000.0; R0603
R4, R5, R10: 4700.0; R0603
R6, R7, R8, R9, R11, R12, R28, R29: 10000.0; R0603
R13, R14, R15: 100000.0; R0603
R16, R17, R18, R19, R20, R21, R22, R23, R24, R25: 34000.0; R0603
R26: 220000.0; R0603
R27: 1000000.0; R0603
R30: 9100.0; R0603
R31: 680000.0; R0603
R32: 120000.0; R0603
U1: STM32L476QGI6; UFBGA132
U2: AT25040B-SSHL-T; SOIC-8
U3: FT232RL-REEL; SSOP-28
U4: 10118193-0001LF; FCI_10118193-0001LF
U5: MAX3218EAP+T; SSOP-20
U6: HTSS-105-01-G-D
U7: mtfc4gmcdm; TFBGA-153
U8: ABLS-25.000MHZ-B2F-T
U9: ABLS-12.000MHZ-B4-T
U10: ASEK-32.768KHz-ECST; ASEK
U11: ltc3406es5; TSOT-23-5
U12: TPS3895ADRYR; SON-6
U13: 4-1437565-2; SW_4-1437565-2
U14: Q65110A2395; LGM67K-G1J2-24-Z
U15, U16: nc7sz125m5x; NC7SZ125M5X

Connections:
CLK_CRYSTAL_U1_F1: C16.1, U1.F1, U8.1
CLK_CRYSTAL_U1_G1: C17.1, U1.G1, U8.2
CLK_CRYSTAL_U3_27: U3.27, U9.1
CLK_CRYSTAL_U3_28: U3.28, U9.2
CLK_U1_D1: U1.D1, U10.3
GND: C1.2, C2.2, C3.2, C4.2, C5.2, C6.2, C7.2, C8.2, C9.2, C10.2, C11.2, C12.2, C13.2, C14.2, C15.2, C16.2, C17.2, C18.2, C19.2, C20.2, C21.2, C22.2, C23.2, C24.2, C25.2, C27.2, C28.2, C29.2, C30.2, C31.2, C32.2, C33.2, C34.2, C35.1, C35.2, C36.2, C37.2, C38.2, C39.2, C40.2, J1.2, R2.2, R6.2, R12.2, R26.2, R30.2, R32.2, U1.D3, U1.E3, U1.F2, U1.F6, U1.F7, U1.F11, U1.F12, U1.J1, U2.4, U3.7, U3.18, U3.21, U3.25, U3.26, U4.5, U4.6, U4.7, U4.8, U4.9, U5.5, U5.17, U5.20, U6.9, U7.C4, U7.E7, U7.G5, U7.H10, U7.K8, U7.N2, U7.N5, U7.P4, U7.P6, U10.2, U11.2, U12.2, U14.C, U15.1, U15.3, U16.1, U16.3
NET_U1_A4: R6.1, U1.A4
NET_U1_H2: R5.1, U1.H2, U16.4
NET_U1_M12: U13.3, U13.4
NET_U2_3: R7.1, U2.3
NET_U2_7: R9.1, U2.7
NET_U3_14: R11.1, U3.14
NET_U3_17: C21.1, U3.17
NET_U3_19: R12.1, U3.19
NET_U4_1: R10.1, U4.1
NET_U4_2: U3.16, U4.2
NET_U4_3: U3.15, U4.3
NET_U5_1: I1.1, U5.1
NET_U5_2: R13.1, U5.2
NET_U5_3: R14.1, U5.3
NET_U5_4: R15.1, U5.4
NET_U5_15: C25.1, U5.15
NET_U5_16: C26.2, U5.16
NET_U5_18: C26.1, U5.18
NET_U5_19: C24.1, U5.19
NET_U6_3: U5.12, U6.3
NET_U6_4: U5.11, U6.4
NET_U6_5: U5.14, U6.5
NET_U6_6: U5.13, U6.6
NET_U7_C2: C29.1, C30.1, U7.C2
NET_U7_K5: R4.1, U7.K5, U15.4
NET_U11_3: I2.1, U11.3
NET_U11_5: R26.1, R27.1, U11.5
NET_U11_ATNET_3: I2.2, R27.2
NET_U12_1: R29.1, R30.1, U12.1
NET_U12_3: R31.2, R32.1, U12.3
NET_U12_4: R28.1, U12.4, U15.2, U16.2
NET_U13_1: R2.1, U13.1, U13.2
PROC_LPUART1_CTS: U1.E9, U3.3
PROC_LPUART1_RTS: U1.G4, U3.11
PROC_LPUART1_RX: U1.H1, U3.1
PROC_LPUART1_TX: U1.H4, U3.5
PROC_SDMMC1_CK: R25.1, U1.B10, U7.M6
PROC_SDMMC1_CMD: R24.1, U1.C8, U7.M5
PROC_SDMMC1_D0: R16.1, U1.E10, U7.A3
PROC_SDMMC1_D1: R17.1, U1.D12, U7.A4
PROC_SDMMC1_D2: R18.1, U1.B11, U7.A5
PROC_SDMMC1_D3: R19.1, U1.C10, U7.B2
PROC_SDMMC1_D4: R20.1, U1.A3, U7.B3
PROC_SDMMC1_D5: R21.1, U1.B3, U7.B4
PROC_SDMMC1_D6: R22.1, U1.E12, U7.B5
PROC_SDMMC1_D7: R23.1, U1.E11, U7.B6
PROC_SPI1_MISO: U1.A7, U2.2
PROC_SPI1_MOSI: U1.C5, U2.5
PROC_SPI1_NSS: R8.1, U1.J4, U2.1
PROC_SPI1_SCK: U1.A8, U2.6
PROC_UART4_CTS: U1.B4, U5.8
PROC_UART4_RTS: U1.A9, U5.10
PROC_UART4_RX: U1.M2, U5.9
PROC_UART4_TX: U1.L2, U5.7
VCC_S1_5V1: C34.1, C37.1, C38.1, J1.1, U11.4
VCC_TIER1_3V3: C1.1, C2.1, C3.1, C4.1, C5.1, C6.1, C7.1, C8.1, C9.1, C10.1, C11.1, C12.1, C13.1, C14.1, C15.1, C18.1, C19.1, C20.1, C22.1, C23.1, C27.1, C28.1, C31.1, C32.1, C33.1, C35.2, C36.1, C39.1, C40.1, I1.2, I2.2, R4.2, R5.2, R7.2, R8.2, R9.2, R11.2, R13.2, R14.2, R15.2, R16.2, R17.2, R18.2, R19.2, R20.2, R21.2, R22.2, R23.2, R24.2, R25.2, R27.2, R28.2, R29.2, R31.1, U1.C4, U1.C11, U1.E2, U1.G2, U1.G6, U1.G7, U1.G11, U1.G12, U1.H3, U1.L1, U1.M1, U2.8, U3.4, U3.20, U5.6, U7.C6, U7.E6, U7.F5, U7.J10, U7.K9, U7.M4, U7.N4, U7.P3, U7.P5, U10.4, U12.6, U15.5, U16.5
